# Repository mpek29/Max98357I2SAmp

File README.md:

# Max98357I2SAmp

## 🚀 Overview

This is an open-source KiCad redesign of the **Adafruit MAX98357 I2S Amp Breakout**, featuring modified input and output connectors using **JST-SH & JST-PH**. This version maintains the compact, efficient, and high-performance Class-D amplifier while enhancing connectivity for ease of integration into various projects.

## 🎯 Purpose

- 🔌 **Enhanced Connectivity**: Uses JST-SH & JST-PH connectors for secure and reliable connections.
- 🎵 **Digital Audio Amplification**: Converts I2S digital audio to amplified analog output.
- 📏 **Compact & Efficient**: Optimized for embedded, IoT, and portable applications.
- 🛠️ **Open-source & Customizable**: Modify the design to fit your needs.

## 📝 Features

| 🏷️ Feature          | 🔍 Description                                                      |
| -------------------- | ------------------------------------------------------------------- |
| 🎵 **I2S Input**     | Accepts standard I2S digital audio format                           |
| 🔊 **Amplification** | Class-D amplifier delivering up to **3.2W into 4Ω**                 |
| 🔌 **Connectors**    | JST-SH for I2S input, JST-PH for speaker output                     |
| ⚡ **Power Supply**   | Operates from **2.7V to 5.5V**                                      |
| 🔥 **Efficiency**    | Class-D architecture with built-in thermal & overcurrent protection |
| 📜 **PCB Design**    | Fully designed in KiCad, optimized for easy manufacturing           |

## 📐 PCB Design Preview

| 📜 Schematic | 🖥️ PCB Layout | 🏗️ 3D |
|-----------|-----------|-----------|
|  |  |  |

**Inspired by Adafruit's MAX98357 I2S Amp Breakout, redesigned for improved connectivity.**

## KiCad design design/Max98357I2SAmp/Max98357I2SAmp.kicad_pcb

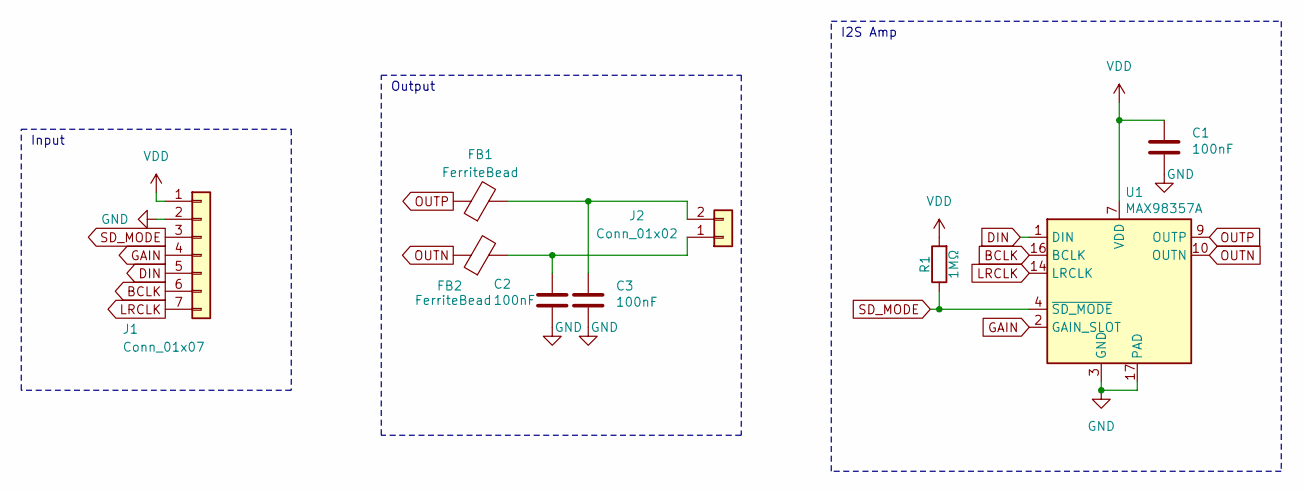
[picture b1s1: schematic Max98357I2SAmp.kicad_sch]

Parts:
C1, C2, C3: 100nF; C_0603_1608Metric_Pad1.08x0.95mm_HandSolder
FB1, FB2: FerriteBead; C_0603_1608Metric_Pad1.08x0.95mm_HandSolder
J1: Conn_01x07; JST_SH_SM07B-SRSS-TB_1x07-1MP_P1.00mm_Horizontal
J2: Conn_01x02; JST_PH_S2B-PH-SM4-TB_1x02-1MP_P2.00mm_Horizontal
R1: 1MΩ; R_0603_1608Metric_Pad0.98x0.95mm_HandSolder
U1: MAX98357A; TQFN-16-1EP_3x3mm_P0.5mm_EP1.23x1.23mm

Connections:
BCLK: J1.6, U1.16 (BCLK)
DIN: J1.5, U1.1 (DIN)
GAIN: J1.4, U1.2 (GAIN_SLOT)
GND: C1.2, C2.2, C3.2, J1.2, U1.3 (GND), U1.11 (GND), U1.15 (GND), U1.17 (PAD)
LRCLK: J1.7, U1.14 (LRCLK)
unnamed: C2.1, FB2.2, J2.1
unnamed: C3.1, FB1.2, J2.2
OUTN: FB2.1, U1.10 (OUTN)
OUTP: FB1.1, U1.9 (OUTP)
SD_MODE: J1.3, R1.1, U1.4 (~SD_MODE)
VDD: C1.1, J1.1, R1.2, U1.7 (VDD), U1.8 (VDD)

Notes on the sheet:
I2S Amp
Input
Output

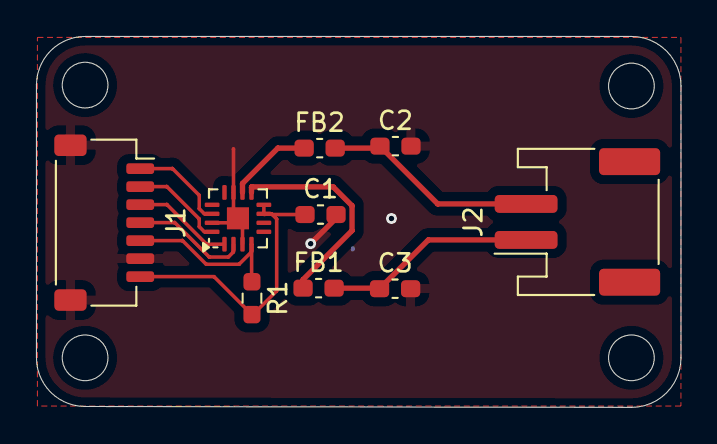
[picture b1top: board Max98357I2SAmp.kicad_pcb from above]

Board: 2 copper layers, 35.8 x 20.6 mm, 9 parts (0 on the bottom side), 11 nets.

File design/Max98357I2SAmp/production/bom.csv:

Designator,Footprint,Quantity,Value,LCSC Part #
"C1, C2, C3",0603,3,100nF,
"FB1, FB2",0603,2,FerriteBead,
J1,JST_SH_SM07B-SRSS-TB_1x07-1MP_P1.00mm_Horizontal,1,Conn_01x07,
J2,JST_PH_S2B-PH-SM4-TB_1x02-1MP_P2.00mm_Horizontal,1,Conn_01x02,
R1,0603,1,1MΩ,
U1,TQFN-16-1EP_3x3mm_P0.5mm_EP1.23x1.23mm,1,MAX98357A,

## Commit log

2025-04-10 adjustement and gerber files
2025-08-30 update pic
